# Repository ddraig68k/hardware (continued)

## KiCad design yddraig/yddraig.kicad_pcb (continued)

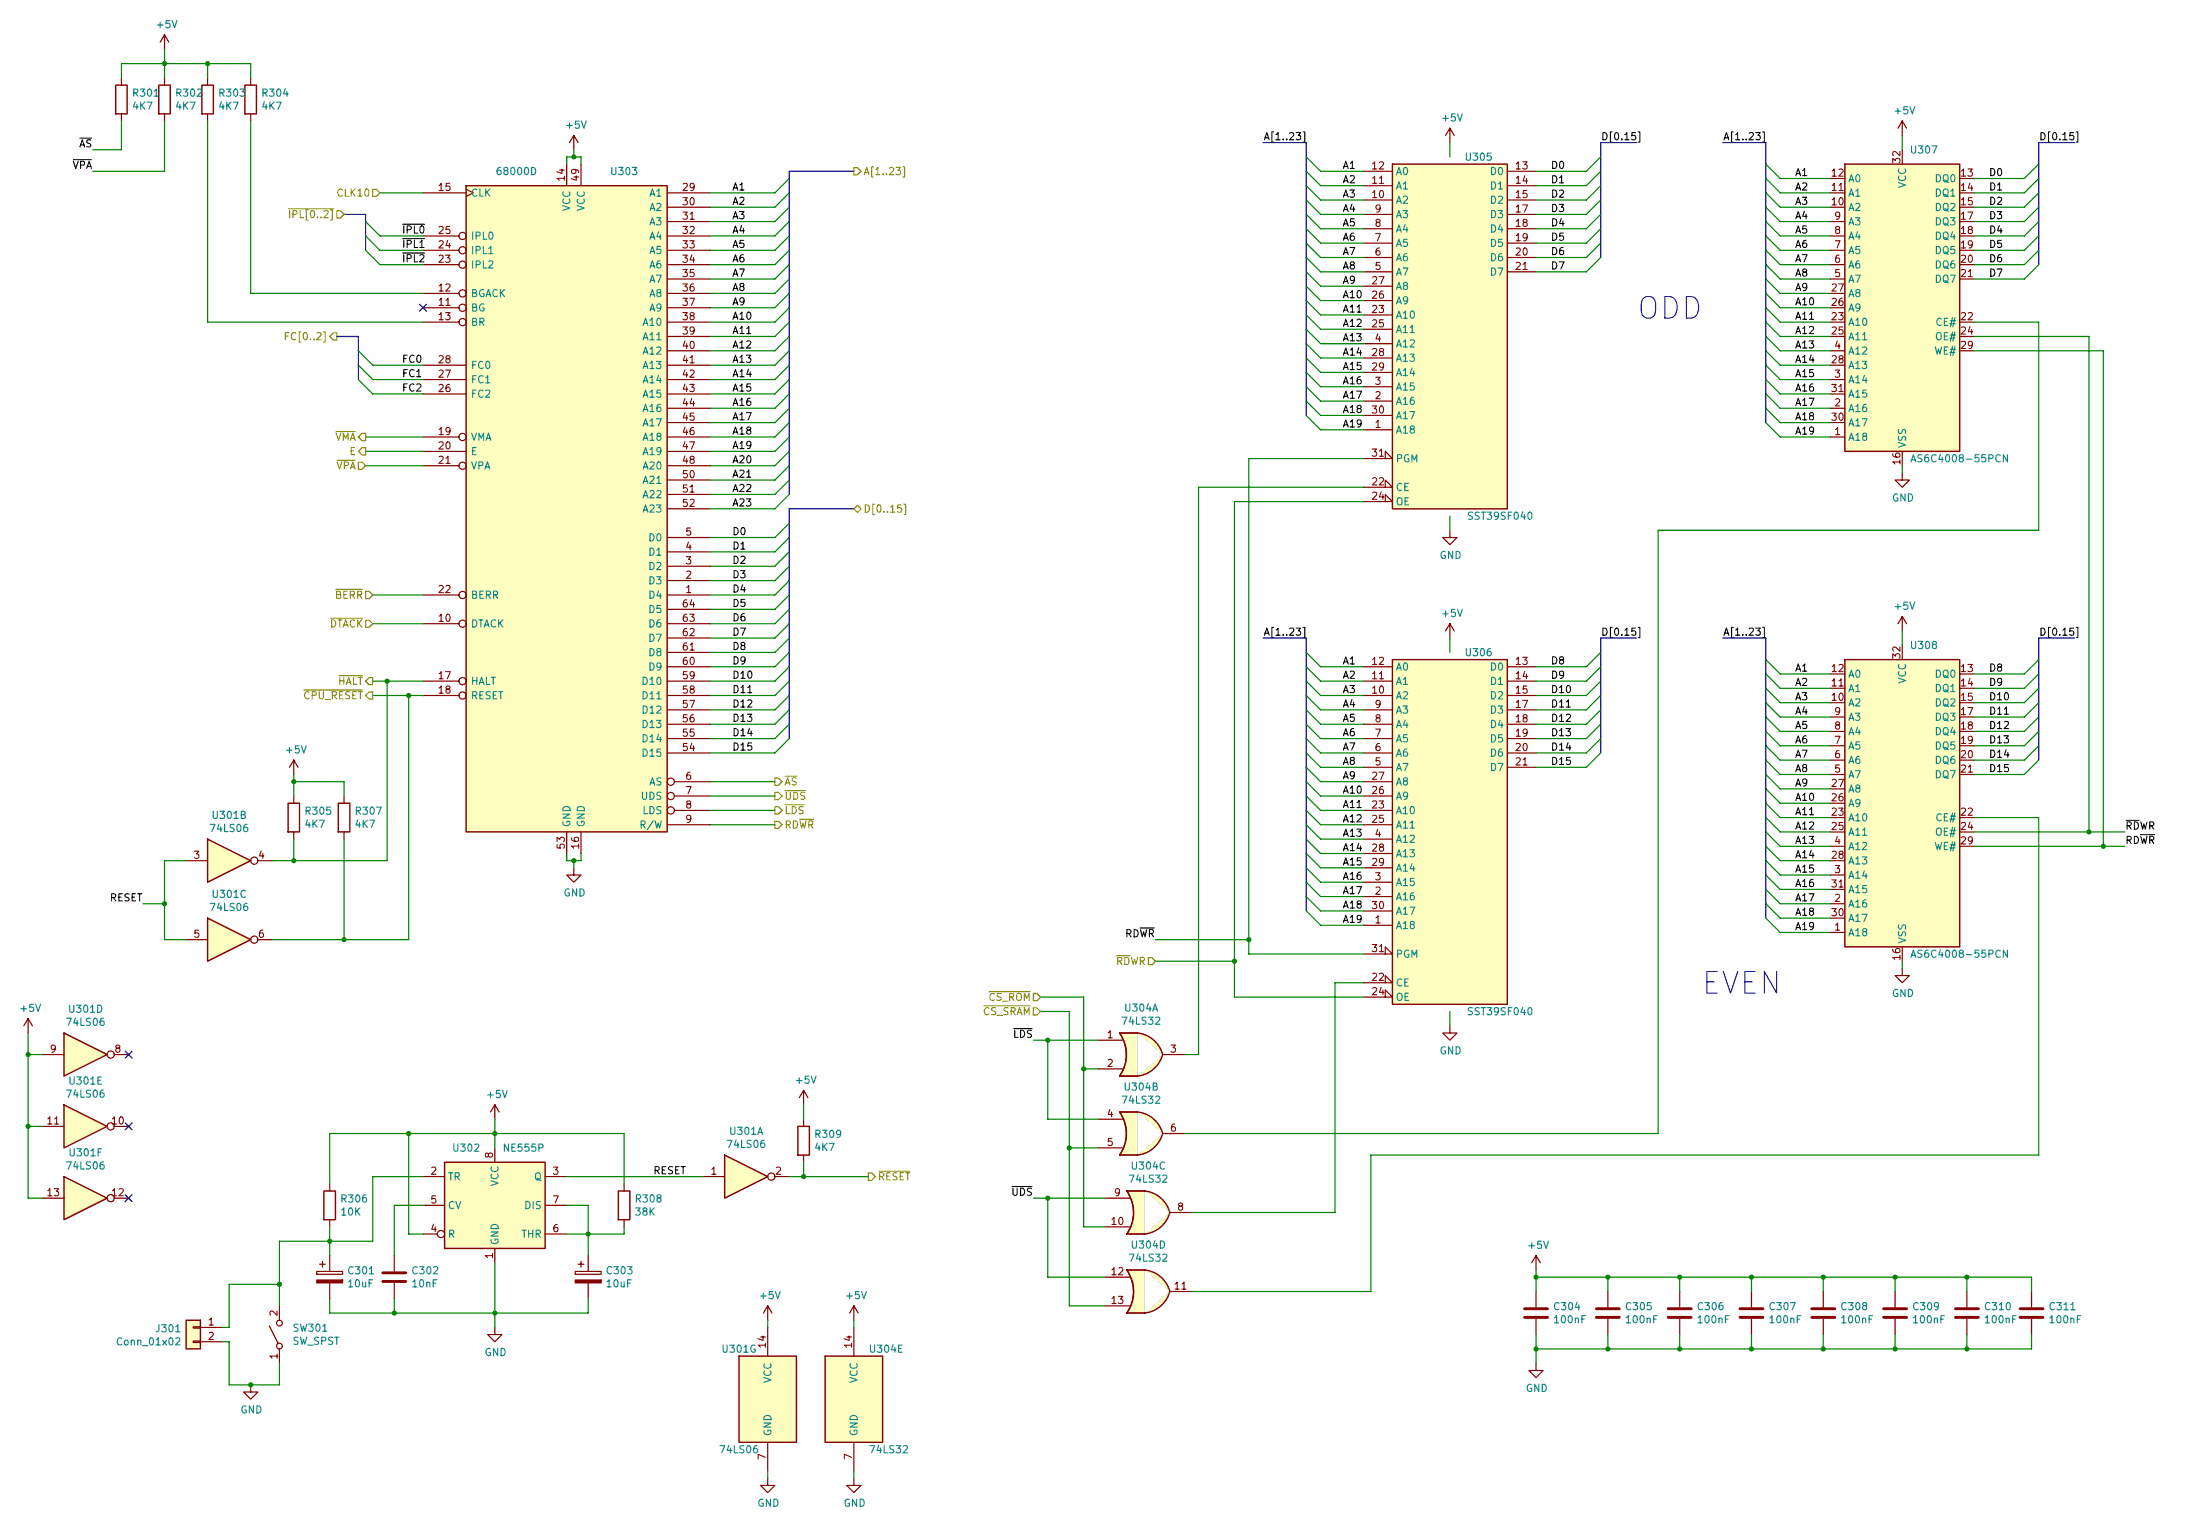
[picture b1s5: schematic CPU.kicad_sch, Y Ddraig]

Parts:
C301, C303: 10uF; CP_Radial_D5.0mm_P2.50mm
C302: 10nF; C_Disc_D3.8mm_W2.6mm_P2.50mm
C304, C305, C306, C307, C308, C309, C310, C311: 100nF; C_Disc_D3.8mm_W2.6mm_P2.50mm
J301: Conn_01x02; PinHeader_1x02_P2.54mm_Vertical
R301, R302, R303, R304, R305, R307, R309: 4K7; R_Axial_DIN0207_L6.3mm_D2.5mm_P10.16mm_Horizontal
R306: 10K; R_Axial_DIN0207_L6.3mm_D2.5mm_P10.16mm_Horizontal
R308: 38K; R_Axial_DIN0207_L6.3mm_D2.5mm_P10.16mm_Horizontal
SW301: SW_SPST; SW_PUSH_6mm_H4.3mm
U301: 74LS06; DIP-14_W7.62mm_Socket
U302: NE555P; DIP-8_W7.62mm
U303: 68000D; DIP-64_W22.86mm_Socket
U304: 74LS32; DIP-14_W7.62mm_Socket
U305, U306: SST39SF040; DIP-32_W15.24mm_Socket
U307, U308: AS6C4008-55PCN; DIP-32_W15.24mm_Socket

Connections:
+5V: C304.1, C305.1, C306.1, C307.1, C308.1, C309.1, C310.1, C311.1, R301.1, R302.1, R303.1, R304.1, R305.1, R306.1, R307.1, R308.1, R309.1, U301.9, U301.11, U301.13, U301.14 (VCC), U302.4 (R), U302.8 (VCC), U303.14 (VCC), U303.49 (VCC), U304.14 (VCC), U305.32 (VCC), U306.32 (VCC), U307.32 (VCC), U308.32 (VCC); also elsewhere on the board
/CPU, RAM and ROM/A1: U303.29 (A1), U305.12 (A0), U306.12 (A0), U307.12 (A0), U308.12 (A0); also elsewhere on the board
/CPU, RAM and ROM/A2: U303.30 (A2), U305.11 (A1), U306.11 (A1), U307.11 (A1), U308.11 (A1); also elsewhere on the board
/CPU, RAM and ROM/A3: U303.31 (A3), U305.10 (A2), U306.10 (A2), U307.10 (A2), U308.10 (A2); also elsewhere on the board
/CPU, RAM and ROM/A4: U303.32 (A4), U305.9 (A3), U306.9 (A3), U307.9 (A3), U308.9 (A3); also elsewhere on the board
/CPU, RAM and ROM/A5: U303.33 (A5), U305.8 (A4), U306.8 (A4), U307.8 (A4), U308.8 (A4); also elsewhere on the board
/CPU, RAM and ROM/A6: U303.34 (A6), U305.7 (A5), U306.7 (A5), U307.7 (A5), U308.7 (A5); also elsewhere on the board
/CPU, RAM and ROM/A7: U303.35 (A7), U305.6 (A6), U306.6 (A6), U307.6 (A6), U308.6 (A6); also elsewhere on the board
/CPU, RAM and ROM/A8: U303.36 (A8), U305.5 (A7), U306.5 (A7), U307.5 (A7), U308.5 (A7); also elsewhere on the board
/CPU, RAM and ROM/A9: U303.37 (A9), U305.27 (A8), U306.27 (A8), U307.27 (A8), U308.27 (A8); also elsewhere on the board
/CPU, RAM and ROM/A10: U303.38 (A10), U305.26 (A9), U306.26 (A9), U307.26 (A9), U308.26 (A9); also elsewhere on the board
/CPU, RAM and ROM/A11: U303.39 (A11), U305.23 (A10), U306.23 (A10), U307.23 (A10), U308.23 (A10); also elsewhere on the board
/CPU, RAM and ROM/A12: U303.40 (A12), U305.25 (A11), U306.25 (A11), U307.25 (A11), U308.25 (A11); also elsewhere on the board
/CPU, RAM and ROM/A13: U303.41 (A13), U305.4 (A12), U306.4 (A12), U307.4 (A12), U308.4 (A12); also elsewhere on the board
/CPU, RAM and ROM/A14: U303.42 (A14), U305.28 (A13), U306.28 (A13), U307.28 (A13), U308.28 (A13); also elsewhere on the board
/CPU, RAM and ROM/A15: U303.43 (A15), U305.29 (A14), U306.29 (A14), U307.3 (A14), U308.3 (A14); also elsewhere on the board
/CPU, RAM and ROM/A16: U303.44 (A16), U305.3 (A15), U306.3 (A15), U307.31 (A15), U308.31 (A15); also elsewhere on the board
/CPU, RAM and ROM/A17: U303.45 (A17), U305.2 (A16), U306.2 (A16), U307.2 (A16), U308.2 (A16); also elsewhere on the board
/CPU, RAM and ROM/A18: U303.46 (A18), U305.30 (A17), U306.30 (A17), U307.30 (A17), U308.30 (A17); also elsewhere on the board
/CPU, RAM and ROM/A19: U303.47 (A19), U305.1 (A18), U306.1 (A18), U307.1 (A18), U308.1 (A18); also elsewhere on the board
/CPU, RAM and ROM/A20: U303.48 (A20); also elsewhere on the board
/CPU, RAM and ROM/A21: U303.50 (A21); also elsewhere on the board
/CPU, RAM and ROM/A22: U303.51 (A22); also elsewhere on the board
/CPU, RAM and ROM/A23: U303.52 (A23); also elsewhere on the board
/CPU, RAM and ROM/CLK10: U303.15 (CLK); also elsewhere on the board
/CPU, RAM and ROM/E: U303.20 (E); also elsewhere on the board
/CPU, RAM and ROM/FC0: U303.28 (FC0); also elsewhere on the board
/CPU, RAM and ROM/FC1: U303.27 (FC1); also elsewhere on the board
/CPU, RAM and ROM/FC2: U303.26 (FC2); also elsewhere on the board
/CPU, RAM and ROM/RD~WR: U303.9 (R/W), U305.31 (PGM), U306.31 (PGM), U307.29 (WE#), U308.29 (WE#); also elsewhere on the board
/CPU, RAM and ROM/RESET: U301.1, U301.3, U301.5, U302.3 (Q)
/CPU, RAM and ROM/~AS: R301.2, U303.6 (AS); also elsewhere on the board
/CPU, RAM and ROM/~BERR: U303.22 (BERR); also elsewhere on the board
/CPU, RAM and ROM/~CS_ROM: U304.2, U304.10; also elsewhere on the board
/CPU, RAM and ROM/~CS_SRAM: U304.5, U304.13; also elsewhere on the board
/CPU, RAM and ROM/~DTACK: U303.10 (DTACK); also elsewhere on the board
/CPU, RAM and ROM/~IPL0: U303.25 (IPL0); also elsewhere on the board
/CPU, RAM and ROM/~IPL1: U303.24 (IPL1); also elsewhere on the board
/CPU, RAM and ROM/~IPL2: U303.23 (IPL2); also elsewhere on the board
/CPU, RAM and ROM/~LDS: U303.8 (LDS), U304.1, U304.4; also elsewhere on the board
/CPU, RAM and ROM/~RDWR: U305.24 (OE), U306.24 (OE), U307.24 (OE#), U308.24 (OE#); also elsewhere on the board
/CPU, RAM and ROM/~UDS: U303.7 (UDS), U304.9, U304.12; also elsewhere on the board
/CPU, RAM and ROM/~VMA: U303.19 (VMA); also elsewhere on the board
/CPU, RAM and ROM/~VPA: R302.2, U303.21 (VPA); also elsewhere on the board
/Decode and Logic/~CPU_RESET: R307.2, U301.6, U303.18 (RESET); also elsewhere on the board
/Decode and Logic/~HALT: R305.2, U301.4, U303.17 (HALT); also elsewhere on the board
/Decode and Logic/~RESET: R309.2, U301.2; also elsewhere on the board
/Peripherals/D0: U303.5 (D0), U305.13 (D0), U307.13 (DQ0); also elsewhere on the board
/Peripherals/D1: U303.4 (D1), U305.14 (D1), U307.14 (DQ1); also elsewhere on the board
/Peripherals/D2: U303.3 (D2), U305.15 (D2), U307.15 (DQ2); also elsewhere on the board
/Peripherals/D3: U303.2 (D3), U305.17 (D3), U307.17 (DQ3); also elsewhere on the board
/Peripherals/D4: U303.1 (D4), U305.18 (D4), U307.18 (DQ4); also elsewhere on the board
/Peripherals/D5: U303.64 (D5), U305.19 (D5), U307.19 (DQ5); also elsewhere on the board
/Peripherals/D6: U303.63 (D6), U305.20 (D6), U307.20 (DQ6); also elsewhere on the board
/Peripherals/D7: U303.62 (D7), U305.21 (D7), U307.21 (DQ7); also elsewhere on the board
/Peripherals/D8: U303.61 (D8), U306.13 (D0), U308.13 (DQ0); also elsewhere on the board
/Peripherals/D9: U303.60 (D9), U306.14 (D1), U308.14 (DQ1); also elsewhere on the board
/Peripherals/D10: U303.59 (D10), U306.15 (D2), U308.15 (DQ2); also elsewhere on the board
/Peripherals/D11: U303.58 (D11), U306.17 (D3), U308.17 (DQ3); also elsewhere on the board
/Peripherals/D12: U303.57 (D12), U306.18 (D4), U308.18 (DQ4); also elsewhere on the board
/Peripherals/D13: U303.56 (D13), U306.19 (D5), U308.19 (DQ5); also elsewhere on the board
/Peripherals/D14: U303.55 (D14), U306.20 (D6), U308.20 (DQ6); also elsewhere on the board
/Peripherals/D15: U303.54 (D15), U306.21 (D7), U308.21 (DQ7); also elsewhere on the board
GND: C301.2, C302.2, C303.2, C304.2, C305.2, C306.2, C307.2, C308.2, C309.2, C310.2, C311.2, J301.2, SW301.1 (A), U301.7 (GND), U302.1 (GND), U303.16 (GND), U303.53 (GND), U304.7 (GND), U305.16 (GND), U306.16 (GND), U307.16 (VSS), U308.16 (VSS); also elsewhere on the board
unnamed: C301.1, J301.1, R306.2, SW301.2 (B), U302.2 (TR)
unnamed: C302.1, U302.5 (CV)
unnamed: C303.1, R308.2, U302.6 (THR), U302.7 (DIS)
unnamed: R304.2, U303.12 (BGACK)
unnamed: R303.2, U303.13 (BR)
unnamed: U304.3, U305.22 (CE)
unnamed: U304.8, U306.22 (CE)
unnamed: U304.6, U307.22 (CE#)
unnamed: U304.11, U308.22 (CE#)

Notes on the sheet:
ODD
EVEN

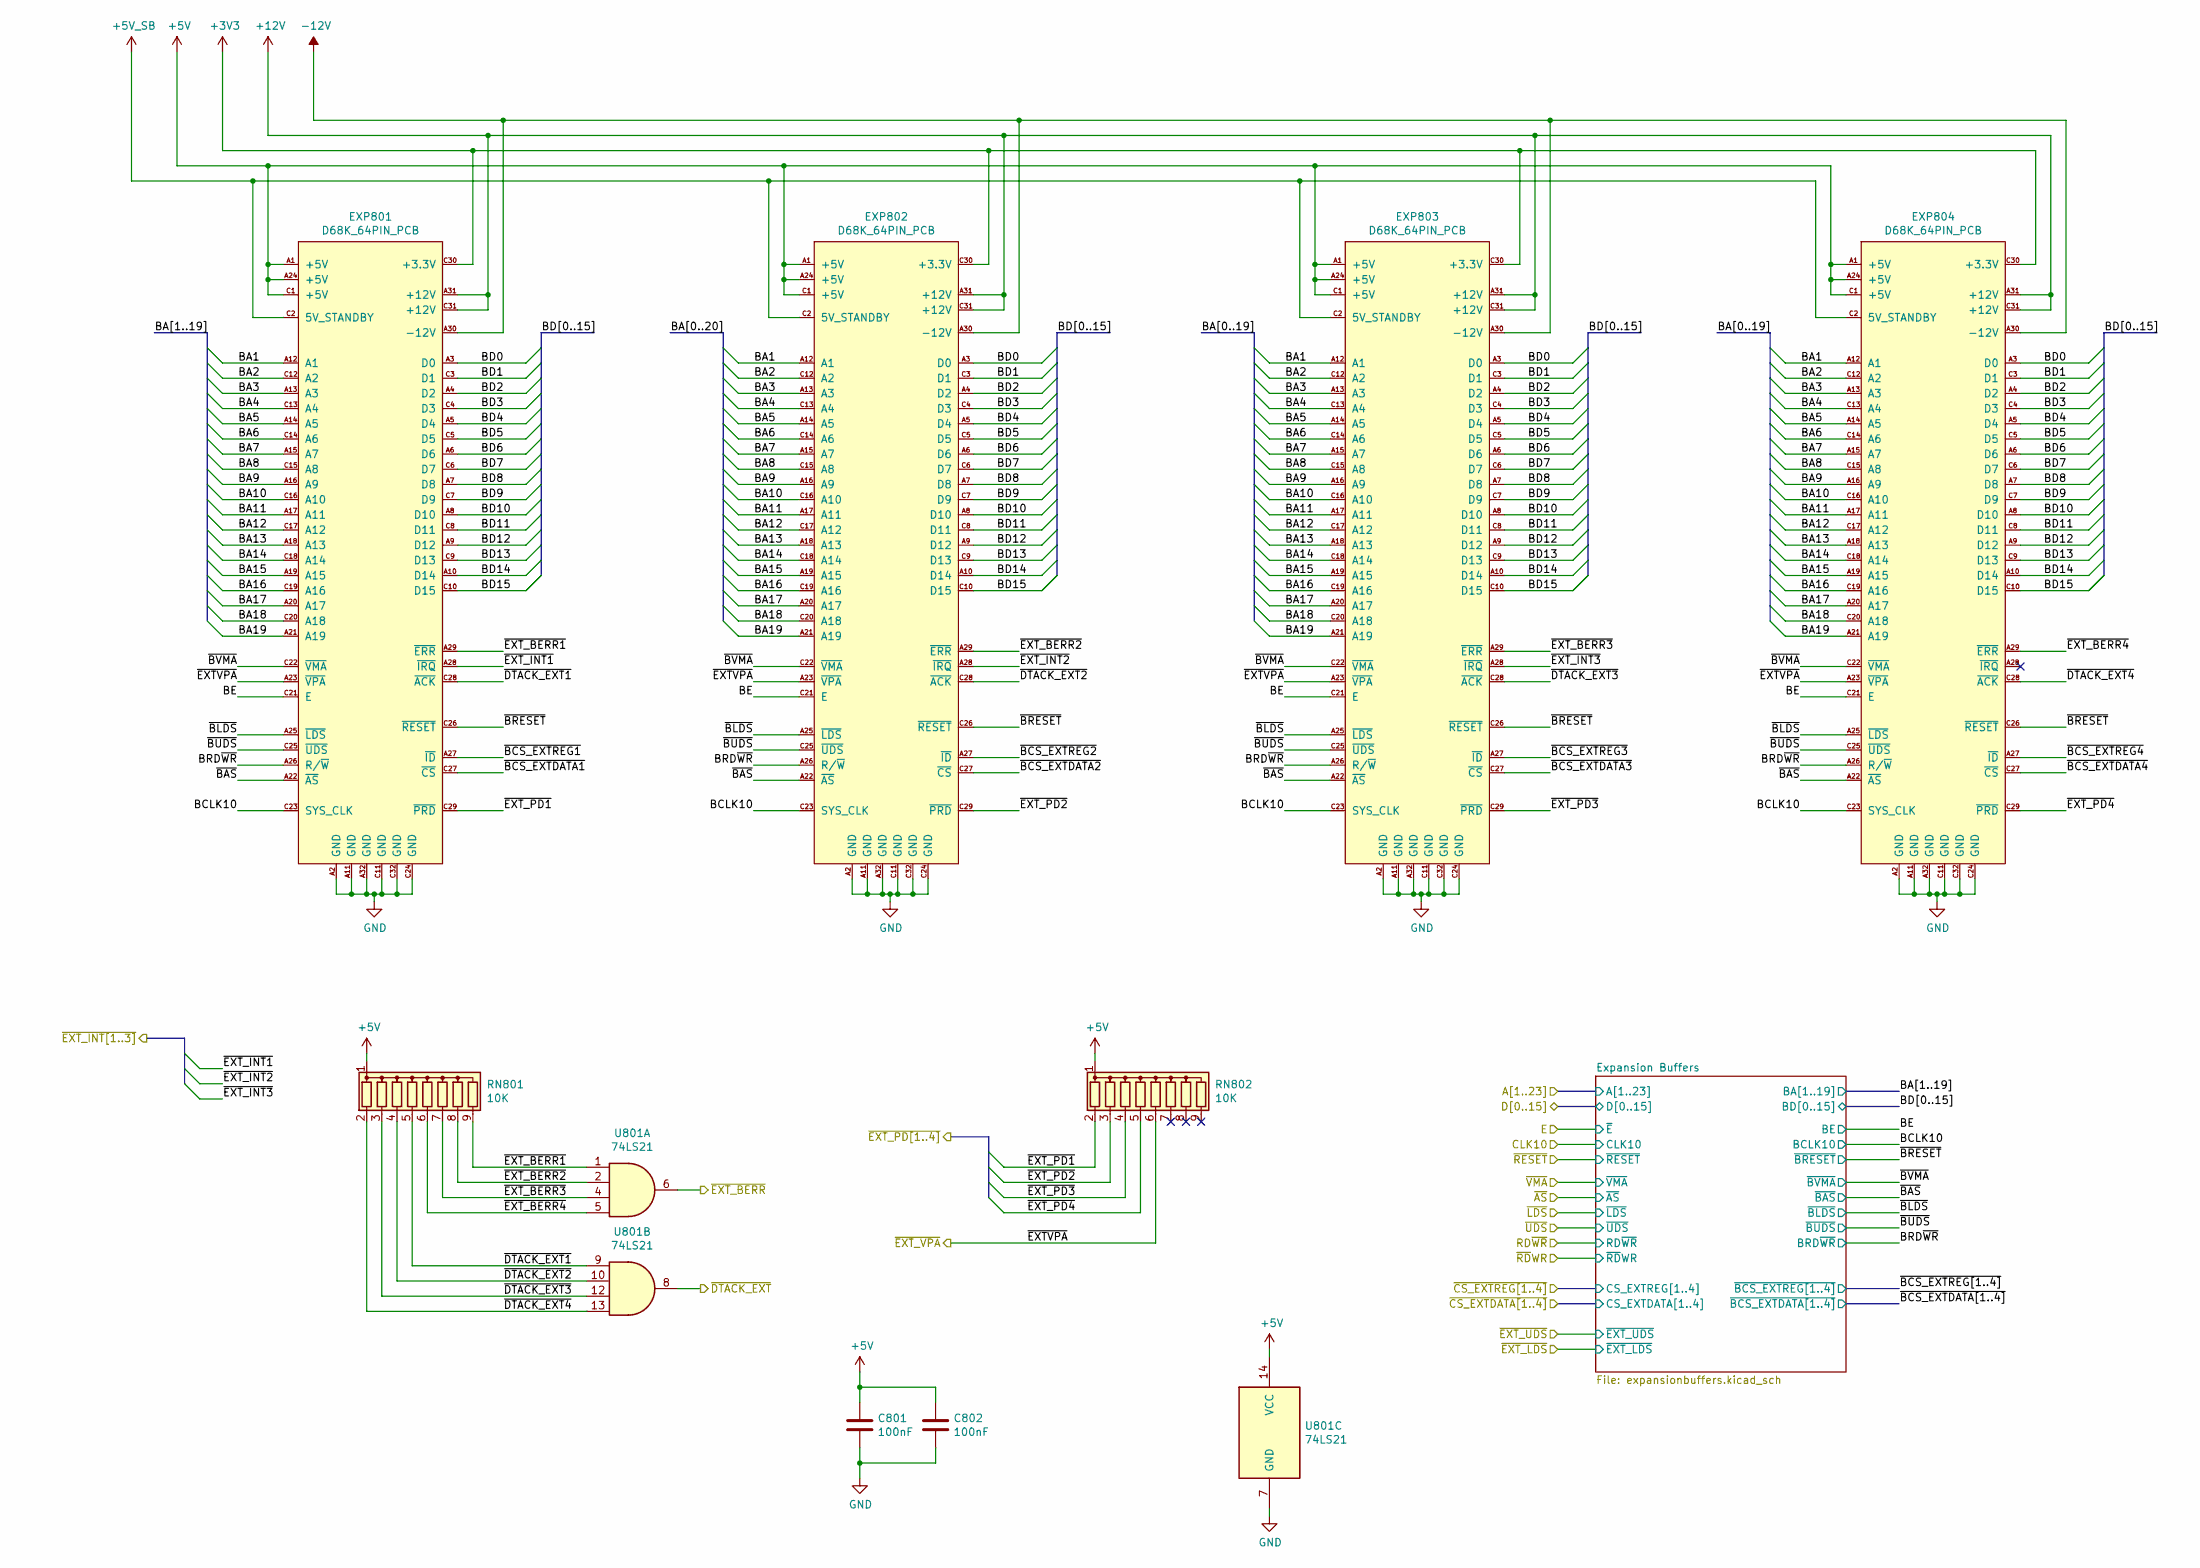
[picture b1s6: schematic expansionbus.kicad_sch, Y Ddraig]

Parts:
C801, C802: 100nF; C_Disc_D3.8mm_W2.6mm_P2.50mm
EXP801, EXP802, EXP803, EXP804: D68K_64PIN_PCB; DIN41612_C_2x32_Female_Vertical_THT
RN801, RN802: 10K; R_Array_SIP9
U801: 74LS21; DIP-14_W7.62mm

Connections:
+3V3: EXP801.C30 (+3.3V), EXP802.C30 (+3.3V), EXP803.C30 (+3.3V), EXP804.C30 (+3.3V); also elsewhere on the board
+5V: C801.1, C802.1, EXP801.A1 (+5V), EXP801.A24 (+5V), EXP801.C1 (+5V), EXP802.A1 (+5V), EXP802.A24 (+5V), EXP802.C1 (+5V), EXP803.A1 (+5V), EXP803.A24 (+5V), EXP803.C1 (+5V), EXP804.A1 (+5V), EXP804.A24 (+5V), EXP804.C1 (+5V), RN801.1 (common), RN802.1 (common), U801.14 (VCC); also elsewhere on the board
+5V_SB: EXP801.C2 (5V_STANDBY), EXP802.C2 (5V_STANDBY), EXP803.C2 (5V_STANDBY), EXP804.C2 (5V_STANDBY); also elsewhere on the board
+12V: EXP801.A31 (+12V), EXP801.C31 (+12V), EXP802.A31 (+12V), EXP802.C31 (+12V), EXP803.A31 (+12V), EXP803.C31 (+12V), EXP804.A31 (+12V), EXP804.C31 (+12V); also elsewhere on the board
-12V: EXP801.A30 (-12V), EXP802.A30 (-12V), EXP803.A30 (-12V), EXP804.A30 (-12V); also elsewhere on the board
/Decode and Logic/~DATCK_EXT: U801.8; also elsewhere on the board
/Decode and Logic/~EXTINT1: EXP801.A28 (~IRQ); also elsewhere on the board
/Decode and Logic/~EXTINT2: EXP802.A28 (~IRQ); also elsewhere on the board
/Decode and Logic/~EXTINT3: EXP803.A28 (~IRQ); also elsewhere on the board
/Decode and Logic/~EXT_BERR: U801.6; also elsewhere on the board
/Expansion Bus/BA1: EXP801.A12 (A1), EXP802.A12 (A1), EXP803.A12 (A1), EXP804.A12 (A1); also elsewhere on the board
/Expansion Bus/BA2: EXP801.C12 (A2), EXP802.C12 (A2), EXP803.C12 (A2), EXP804.C12 (A2); also elsewhere on the board
/Expansion Bus/BA3: EXP801.A13 (A3), EXP802.A13 (A3), EXP803.A13 (A3), EXP804.A13 (A3); also elsewhere on the board
/Expansion Bus/BA4: EXP801.C13 (A4), EXP802.C13 (A4), EXP803.C13 (A4), EXP804.C13 (A4); also elsewhere on the board
/Expansion Bus/BA5: EXP801.A14 (A5), EXP802.A14 (A5), EXP803.A14 (A5), EXP804.A14 (A5); also elsewhere on the board
/Expansion Bus/BA6: EXP801.C14 (A6), EXP802.C14 (A6), EXP803.C14 (A6), EXP804.C14 (A6); also elsewhere on the board
/Expansion Bus/BA7: EXP801.A15 (A7), EXP802.A15 (A7), EXP803.A15 (A7), EXP804.A15 (A7); also elsewhere on the board
/Expansion Bus/BA8: EXP801.C15 (A8), EXP802.C15 (A8), EXP803.C15 (A8), EXP804.C15 (A8); also elsewhere on the board
/Expansion Bus/BA9: EXP801.A16 (A9), EXP802.A16 (A9), EXP803.A16 (A9), EXP804.A16 (A9); also elsewhere on the board
/Expansion Bus/BA10: EXP801.C16 (A10), EXP802.C16 (A10), EXP803.C16 (A10), EXP804.C16 (A10); also elsewhere on the board
/Expansion Bus/BA11: EXP801.A17 (A11), EXP802.A17 (A11), EXP803.A17 (A11), EXP804.A17 (A11); also elsewhere on the board
/Expansion Bus/BA12: EXP801.C17 (A12), EXP802.C17 (A12), EXP803.C17 (A12), EXP804.C17 (A12); also elsewhere on the board
/Expansion Bus/BA13: EXP801.A18 (A13), EXP802.A18 (A13), EXP803.A18 (A13), EXP804.A18 (A13); also elsewhere on the board
/Expansion Bus/BA14: EXP801.C18 (A14), EXP802.C18 (A14), EXP803.C18 (A14), EXP804.C18 (A14); also elsewhere on the board
/Expansion Bus/BA15: EXP801.A19 (A15), EXP802.A19 (A15), EXP803.A19 (A15), EXP804.A19 (A15); also elsewhere on the board
/Expansion Bus/BA16: EXP801.C19 (A16), EXP802.C19 (A16), EXP803.C19 (A16), EXP804.C19 (A16); also elsewhere on the board
/Expansion Bus/BA17: EXP801.A20 (A17), EXP802.A20 (A17), EXP803.A20 (A17), EXP804.A20 (A17); also elsewhere on the board
/Expansion Bus/BA18: EXP801.C20 (A18), EXP802.C20 (A18), EXP803.C20 (A18), EXP804.C20 (A18); also elsewhere on the board
/Expansion Bus/BA19: EXP801.A21 (A19), EXP802.A21 (A19), EXP803.A21 (A19), EXP804.A21 (A19); also elsewhere on the board
/Expansion Bus/BCLK10: EXP801.C23 (SYS_CLK), EXP802.C23 (SYS_CLK), EXP803.C23 (SYS_CLK), EXP804.C23 (SYS_CLK); also elsewhere on the board
/Expansion Bus/BD0: EXP801.A3 (D0), EXP802.A3 (D0), EXP803.A3 (D0), EXP804.A3 (D0); also elsewhere on the board
/Expansion Bus/BD1: EXP801.C3 (D1), EXP802.C3 (D1), EXP803.C3 (D1), EXP804.C3 (D1); also elsewhere on the board
/Expansion Bus/BD2: EXP801.A4 (D2), EXP802.A4 (D2), EXP803.A4 (D2), EXP804.A4 (D2); also elsewhere on the board
/Expansion Bus/BD3: EXP801.C4 (D3), EXP802.C4 (D3), EXP803.C4 (D3), EXP804.C4 (D3); also elsewhere on the board
/Expansion Bus/BD4: EXP801.A5 (D4), EXP802.A5 (D4), EXP803.A5 (D4), EXP804.A5 (D4); also elsewhere on the board
/Expansion Bus/BD5: EXP801.C5 (D5), EXP802.C5 (D5), EXP803.C5 (D5), EXP804.C5 (D5); also elsewhere on the board
/Expansion Bus/BD6: EXP801.A6 (D6), EXP802.A6 (D6), EXP803.A6 (D6), EXP804.A6 (D6); also elsewhere on the board
/Expansion Bus/BD7: EXP801.C6 (D7), EXP802.C6 (D7), EXP803.C6 (D7), EXP804.C6 (D7); also elsewhere on the board
/Expansion Bus/BD8: EXP801.A7 (D8), EXP802.A7 (D8), EXP803.A7 (D8), EXP804.A7 (D8); also elsewhere on the board
/Expansion Bus/BD9: EXP801.C7 (D9), EXP802.C7 (D9), EXP803.C7 (D9), EXP804.C7 (D9); also elsewhere on the board
/Expansion Bus/BD10: EXP801.A8 (D10), EXP802.A8 (D10), EXP803.A8 (D10), EXP804.A8 (D10); also elsewhere on the board
/Expansion Bus/BD11: EXP801.C8 (D11), EXP802.C8 (D11), EXP803.C8 (D11), EXP804.C8 (D11); also elsewhere on the board
/Expansion Bus/BD12: EXP801.A9 (D12), EXP802.A9 (D12), EXP803.A9 (D12), EXP804.A9 (D12); also elsewhere on the board
/Expansion Bus/BD13: EXP801.C9 (D13), EXP802.C9 (D13), EXP803.C9 (D13), EXP804.C9 (D13); also elsewhere on the board
/Expansion Bus/BD14: EXP801.A10 (D14), EXP802.A10 (D14), EXP803.A10 (D14), EXP804.A10 (D14); also elsewhere on the board
/Expansion Bus/BD15: EXP801.C10 (D15), EXP802.C10 (D15), EXP803.C10 (D15), EXP804.C10 (D15); also elsewhere on the board
/Expansion Bus/BE: EXP801.C21 (E), EXP802.C21 (E), EXP803.C21 (E), EXP804.C21 (E); also elsewhere on the board
/Expansion Bus/BRD~WR: EXP801.A26 (R/~W), EXP802.A26 (R/~W), EXP803.A26 (R/~W), EXP804.A26 (R/~W); also elsewhere on the board
/Expansion Bus/~BAS: EXP801.A22 (~AS), EXP802.A22 (~AS), EXP803.A22 (~AS), EXP804.A22 (~AS); also elsewhere on the board
/Expansion Bus/~BCS_EXTDATA1: EXP801.C27 (~CS); also elsewhere on the board
/Expansion Bus/~BCS_EXTDATA2: EXP802.C27 (~CS); also elsewhere on the board
/Expansion Bus/~BCS_EXTDATA3: EXP803.C27 (~CS); also elsewhere on the board
/Expansion Bus/~BCS_EXTDATA4: EXP804.C27 (~CS); also elsewhere on the board
/Expansion Bus/~BCS_EXTREG1: EXP801.A27 (~ID); also elsewhere on the board
/Expansion Bus/~BCS_EXTREG2: EXP802.A27 (~ID); also elsewhere on the board
/Expansion Bus/~BCS_EXTREG3: EXP803.A27 (~ID); also elsewhere on the board
/Expansion Bus/~BCS_EXTREG4: EXP804.A27 (~ID); also elsewhere on the board
/Expansion Bus/~BLDS: EXP801.A25 (~LDS), EXP802.A25 (~LDS), EXP803.A25 (~LDS), EXP804.A25 (~LDS); also elsewhere on the board
/Expansion Bus/~BRESET: EXP801.C26 (~RESET), EXP802.C26 (~RESET), EXP803.C26 (~RESET), EXP804.C26 (~RESET); also elsewhere on the board
/Expansion Bus/~BUDS: EXP801.C25 (~UDS), EXP802.C25 (~UDS), EXP803.C25 (~UDS), EXP804.C25 (~UDS); also elsewhere on the board
/Expansion Bus/~BVMA: EXP801.C22 (~VMA), EXP802.C22 (~VMA), EXP803.C22 (~VMA), EXP804.C22 (~VMA); also elsewhere on the board
/Expansion Bus/~DTACK_EXT1: EXP801.C28 (~ACK), RN801.5 (R4), U801.9
/Expansion Bus/~DTACK_EXT2: EXP802.C28 (~ACK), RN801.4 (R3), U801.10
/Expansion Bus/~DTACK_EXT3: EXP803.C28 (~ACK), RN801.3 (R2), U801.12
/Expansion Bus/~DTACK_EXT4: EXP804.C28 (~ACK), RN801.2 (R1), U801.13
/Expansion Bus/~EXTVPA: EXP801.A23 (~VPA), EXP802.A23 (~VPA), EXP803.A23 (~VPA), EXP804.A23 (~VPA), RN802.6 (R5); also elsewhere on the board
/Expansion Bus/~EXT_BERR1: EXP801.A29 (~ERR), RN801.9 (R8), U801.1
/Expansion Bus/~EXT_BERR2: EXP802.A29 (~ERR), RN801.8 (R7), U801.2
/Expansion Bus/~EXT_BERR3: EXP803.A29 (~ERR), RN801.7 (R6), U801.4
/Expansion Bus/~EXT_BERR4: EXP804.A29 (~ERR), RN801.6 (R5), U801.5
/Expansion Bus/~EXT_PD1: EXP801.C29 (~PRD), RN802.2 (R1); also elsewhere on the board
/Expansion Bus/~EXT_PD2: EXP802.C29 (~PRD), RN802.3 (R2); also elsewhere on the board
/Expansion Bus/~EXT_PD3: EXP803.C29 (~PRD), RN802.4 (R3); also elsewhere on the board
/Expansion Bus/~EXT_PD4: EXP804.C29 (~PRD), RN802.5 (R4); also elsewhere on the board
GND: C801.2, C802.2, EXP801.A2 (GND), EXP801.A11 (GND), EXP801.A32 (GND), EXP801.C11 (GND), EXP801.C24 (GND), EXP801.C32 (GND), EXP802.A2 (GND), EXP802.A11 (GND), EXP802.A32 (GND), EXP802.C11 (GND), EXP802.C24 (GND), EXP802.C32 (GND), EXP803.A2 (GND), EXP803.A11 (GND), EXP803.A32 (GND), EXP803.C11 (GND), EXP803.C24 (GND), EXP803.C32 (GND), EXP804.A2 (GND), EXP804.A11 (GND), EXP804.A32 (GND), EXP804.C11 (GND), EXP804.C24 (GND), EXP804.C32 (GND), U801.7 (GND); also elsewhere on the board

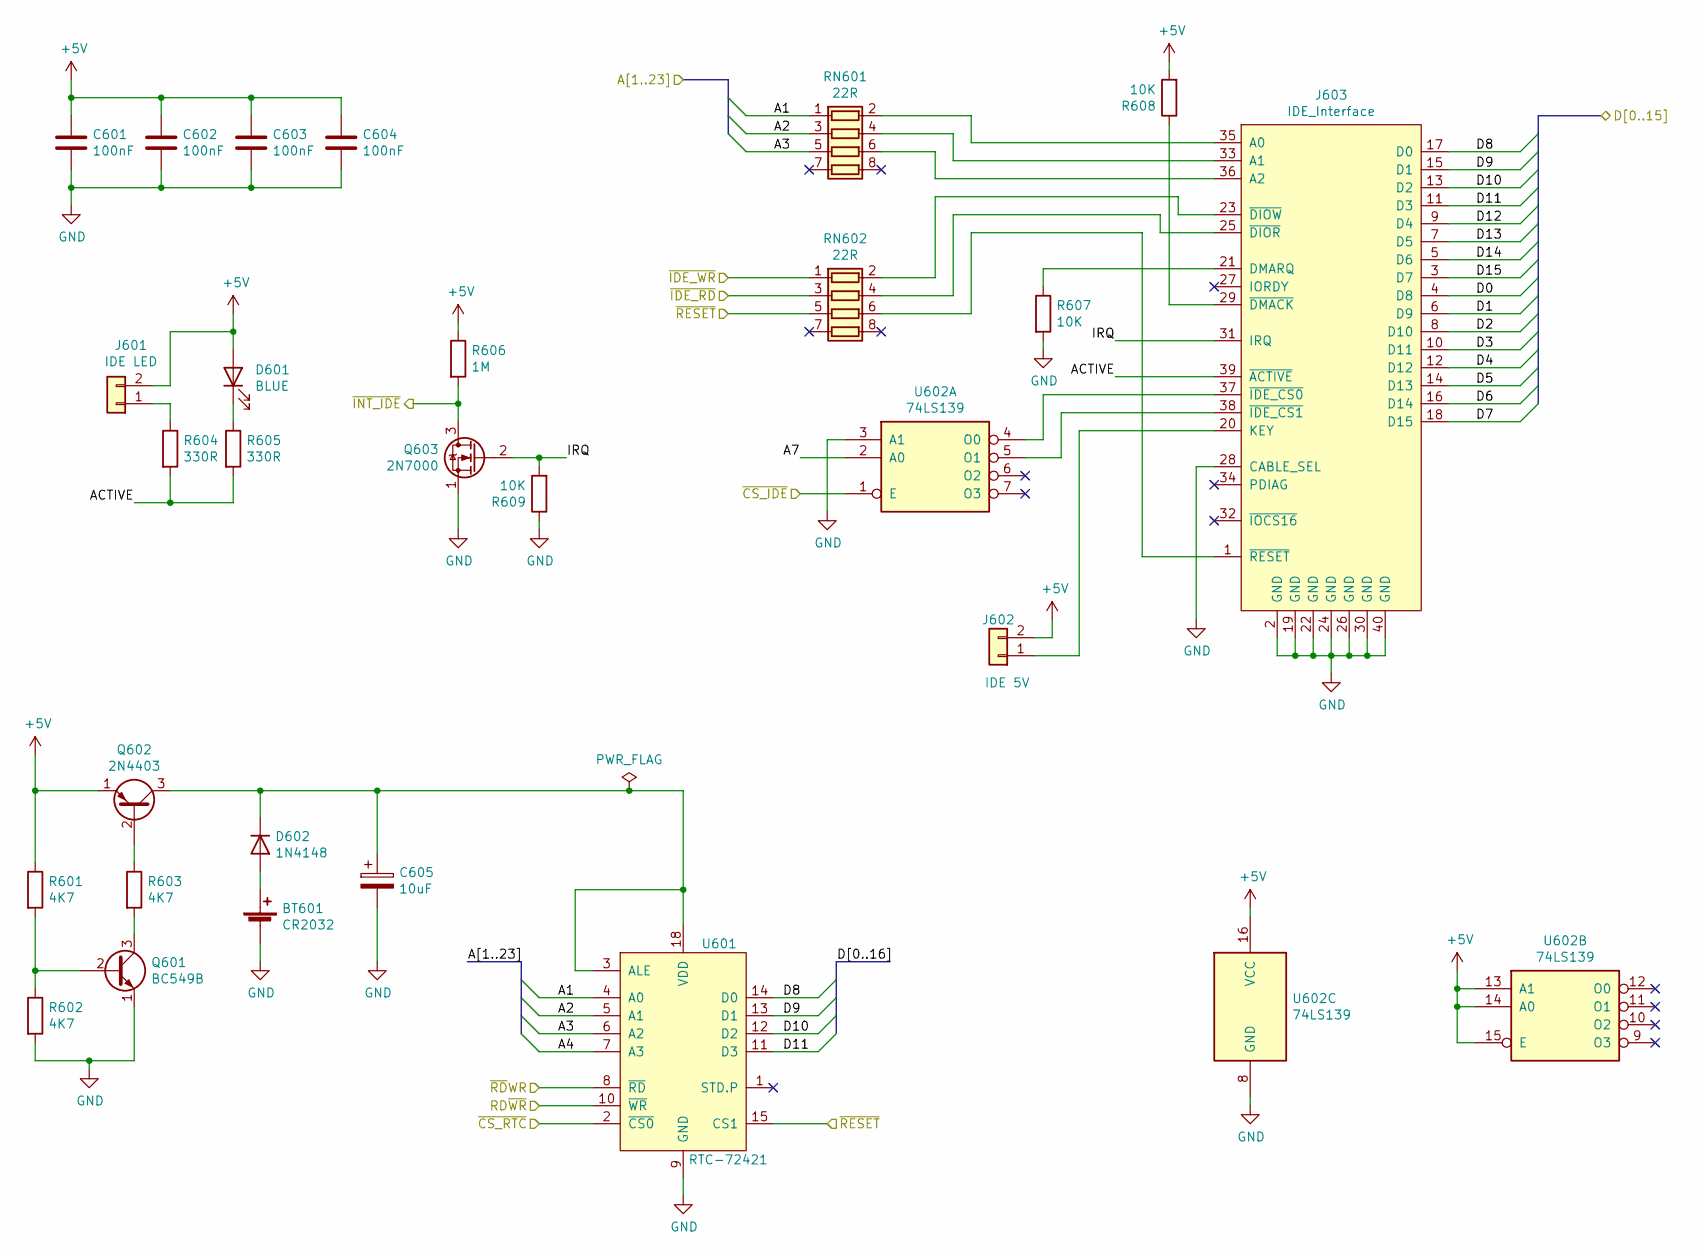
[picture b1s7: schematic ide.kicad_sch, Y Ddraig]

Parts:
BT601: CR2032; BatteryHolder_Keystone_103_1x20mm
C601, C602, C603, C604: 100nF; C_Disc_D3.8mm_W2.6mm_P2.50mm
C605: 10uF; CP_Radial_D5.0mm_P2.50mm
D601: BLUE; LED_D5.0mm
D602: 1N4148; D_DO-35_SOD27_P7.62mm_Horizontal
J601: IDE LED; PinHeader_1x02_P2.54mm_Vertical
J602: IDE 5V; PinHeader_1x02_P2.54mm_Vertical
J603: IDE_Interface; IDC-Header_2x20_P2.54mm_Vertical
Q601: BC549B; TO-92
Q602: 2N4403; TO-92
Q603: 2N7000; TO-92_Inline
R601, R602, R603: 4K7; R_Axial_DIN0207_L6.3mm_D2.5mm_P10.16mm_Horizontal
R604, R605: 330R; R_Axial_DIN0207_L6.3mm_D2.5mm_P10.16mm_Horizontal
R606: 1M; R_Axial_DIN0207_L6.3mm_D2.5mm_P10.16mm_Horizontal
R607, R608, R609: 10K; R_Axial_DIN0207_L6.3mm_D2.5mm_P10.16mm_Horizontal
RN601, RN602: 22R; R_Array_SIP8
U601: RTC-72421; DIP-18_W7.62mm_Socket
U602: 74LS139; DIP-16_W7.62mm_Socket

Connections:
+5V: C601.1, C602.1, C603.1, C604.1, D601.2 (A), J601.2, J602.2, Q602.1 (E), R601.1, R606.1, R608.2, U602.13 (A1), U602.14 (A0), U602.15 (E), U602.16 (VCC); also elsewhere on the board
/CPU, RAM and ROM/A1: RN601.1 (R1.1), U601.4 (A0); also elsewhere on the board
/CPU, RAM and ROM/A2: RN601.3 (R2.1), U601.5 (A1); also elsewhere on the board
/CPU, RAM and ROM/A3: RN601.5 (R3.1), U601.6 (A2); also elsewhere on the board
/CPU, RAM and ROM/A4: U601.7 (A3); also elsewhere on the board
/CPU, RAM and ROM/A7: U602.2 (A0); also elsewhere on the board
/CPU, RAM and ROM/RD~WR: U601.10 (~WR); also elsewhere on the board
/CPU, RAM and ROM/~RDWR: U601.8 (~RD); also elsewhere on the board
/Decode and Logic/~CS_IDE: U602.1 (E); also elsewhere on the board
/Decode and Logic/~CS_RTC: U601.2 (~CS0); also elsewhere on the board
/Decode and Logic/~IDE_RD: RN602.3 (R2.1); also elsewhere on the board
/Decode and Logic/~IDE_WR: RN602.1 (R1.1); also elsewhere on the board
/Decode and Logic/~INT_IDE: Q603.3 (D), R606.2; also elsewhere on the board
/Decode and Logic/~RESET: RN602.5 (R3.1), U601.15 (CS1); also elsewhere on the board
/IDE Interface/ACTIVE: J603.39 (~ACTIVE), R604.2, R605.2
/IDE Interface/IRQ: J603.31 (IRQ), Q603.2 (G), R609.2
/Peripherals/D0: J603.4 (D8); also elsewhere on the board
/Peripherals/D1: J603.6 (D9); also elsewhere on the board
/Peripherals/D2: J603.8 (D10); also elsewhere on the board
/Peripherals/D3: J603.10 (D11); also elsewhere on the board
/Peripherals/D4: J603.12 (D12); also elsewhere on the board
/Peripherals/D5: J603.14 (D13); also elsewhere on the board
/Peripherals/D6: J603.16 (D14); also elsewhere on the board
/Peripherals/D7: J603.18 (D15); also elsewhere on the board
/Peripherals/D8: J603.17 (D0), U601.14 (D0); also elsewhere on the board
/Peripherals/D9: J603.15 (D1), U601.13 (D1); also elsewhere on the board
/Peripherals/D10: J603.13 (D2), U601.12 (D2); also elsewhere on the board
/Peripherals/D11: J603.11 (D3), U601.11 (D3); also elsewhere on the board
/Peripherals/D12: J603.9 (D4); also elsewhere on the board
/Peripherals/D13: J603.7 (D5); also elsewhere on the board
/Peripherals/D14: J603.5 (D6); also elsewhere on the board
/Peripherals/D15: J603.3 (D7); also elsewhere on the board
GND: BT601.2 (-), C601.2, C602.2, C603.2, C604.2, C605.2, J603.2 (GND), J603.19 (GND), J603.22 (GND), J603.24 (GND), J603.26 (GND), J603.28 (CABLE_SEL), J603.30 (GND), J603.40 (GND), Q601.1 (E), Q603.1 (S), R602.2, R607.2, R609.1, U601.9 (GND), U602.3 (A1), U602.8 (GND); also elsewhere on the board
unnamed: BT601.1 (+), D602.2 (A)
unnamed: D601.1 (K), R605.1
unnamed: C605.1, D602.1 (K), Q602.3 (C), U601.3 (ALE), U601.18 (VDD)
unnamed: J601.1, R604.1
unnamed: J602.1, J603.20 (KEY)
unnamed: J603.35 (A0), RN601.2 (R1.2)
unnamed: J603.33 (A1), RN601.4 (R2.2)
unnamed: J603.36 (A2), RN601.6 (R3.2)
unnamed: J603.21 (DMARQ), R607.1
unnamed: J603.25 (~DIOR), RN602.4 (R2.2)
unnamed: J603.23 (~DIOW), RN602.2 (R1.2)
unnamed: J603.29 (~DMACK), R608.1
unnamed: J603.37 (~IDE_CS0), U602.4 (O0)
unnamed: J603.38 (~IDE_CS1), U602.5 (O1)
unnamed: J603.1 (~RESET), RN602.6 (R3.2)
unnamed: Q601.2 (B), R601.2, R602.1
unnamed: Q601.3 (C), R603.2
unnamed: Q602.2 (B), R603.1
